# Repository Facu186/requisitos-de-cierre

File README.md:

# requisitos-de-cierre

Nosotros hicimos el proyecto de sensor de temperatura y humedad implementado junto a un display y un buzzer. Los integrantes del proyecto somos: Romero Julian, Jhonatan Rea Vera, Solis Tobias y Przybylski Facundo.

El link de nuestra pagina del proyecto: https://facu186.github.io/requisitos-de-cierre/

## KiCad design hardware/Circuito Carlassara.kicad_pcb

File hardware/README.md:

En el directorio Hardware encontraremos el circuito esquematico, el PCB y y los datasheets de los elementos utilizados para nuestro proyecto.

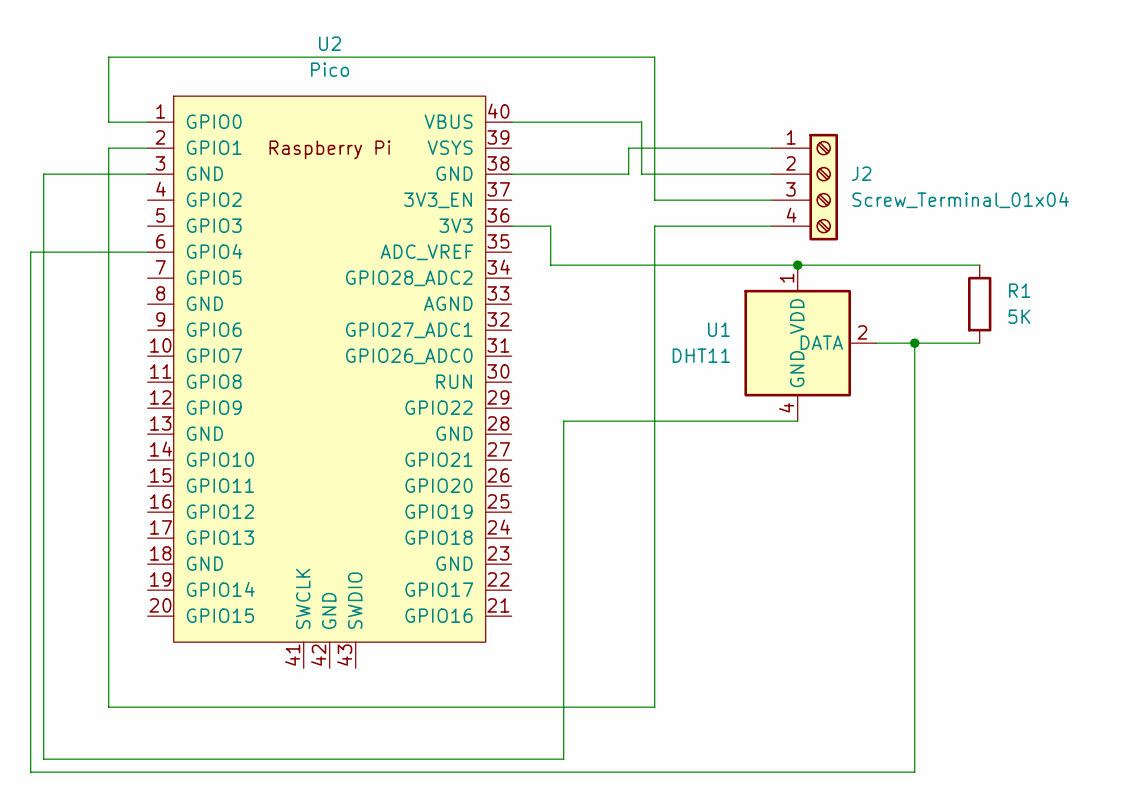
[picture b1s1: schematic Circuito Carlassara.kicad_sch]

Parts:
J2: Screw_Terminal_01x04; TerminalBlock_Phoenix_MKDS-1,5-4_1x04_P5.00mm_Horizontal
R1: 5K; R_Axial_DIN0204_L3.6mm_D1.6mm_P5.08mm_Horizontal
U1: DHT11; Aosong_DHT11_5.5x12.0_P2.54mm
U2: Pico; PinHeader_2x22_P1.00mm_Vertical

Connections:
unnamed: J2.1, U2.38 (GND)
unnamed: J2.2, U2.40 (VBUS)
unnamed: J2.3, U2.1 (GPIO0)
unnamed: J2.4, U2.2 (GPIO1)
unnamed: R1.2, U1.2 (DATA), U2.6 (GPIO4)
unnamed: U1.4 (GND), U2.3 (GND)
unnamed: R1.1, U1.1 (VDD), U2.36 (3V3)

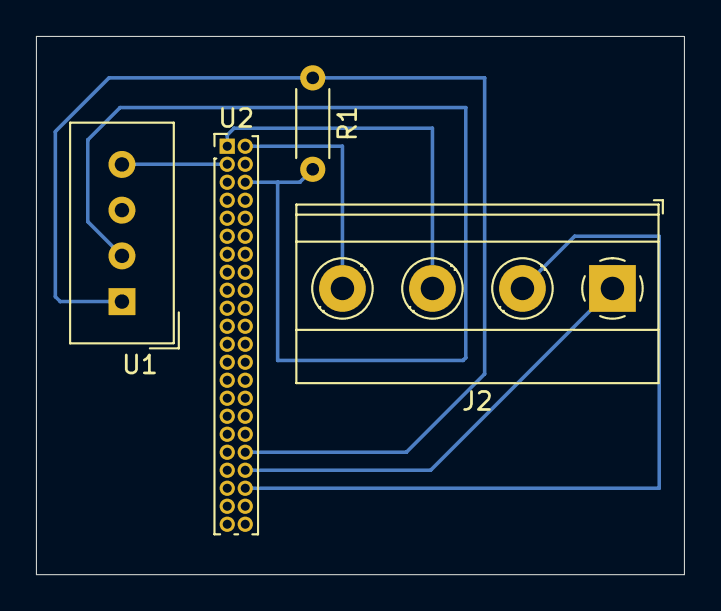
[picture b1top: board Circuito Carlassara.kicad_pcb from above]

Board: 2 copper layers, 36.0 x 29.9 mm, 4 parts (0 on the bottom side), 7 nets.

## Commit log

2024-12-01 Directorio hardware
2024-12-01 Create Directorio firmware
2024-12-01 Create Información Circuito Esquemático
2024-12-01 Create jaja
2024-12-01 Rename imagen_2024-12-01_120508476.png to PCB.png
2024-12-01 Rename imagen_2024-12-01_120848916.png to Circuito Esquematico.png
2024-12-01 Create Programa Implementado Para Nuestro Microcontrolador
2024-12-02 Create Código y librerías utilizadas
2024-12-02 Create Codigo y Librerias Utilizadas
2024-12-02 Rename Codigo y Librerias Utilizadas to Codigo y Librerias Utilizadasmain.py
2024-12-02 Update Programa Implementado Para Nuestro Microcontrolador
2024-12-02 main.py
